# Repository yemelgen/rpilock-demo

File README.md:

This is my first project I have ever done with Rasperry PI.

It's simple and should be good as a learning example. 

I hope someone might find it useful.

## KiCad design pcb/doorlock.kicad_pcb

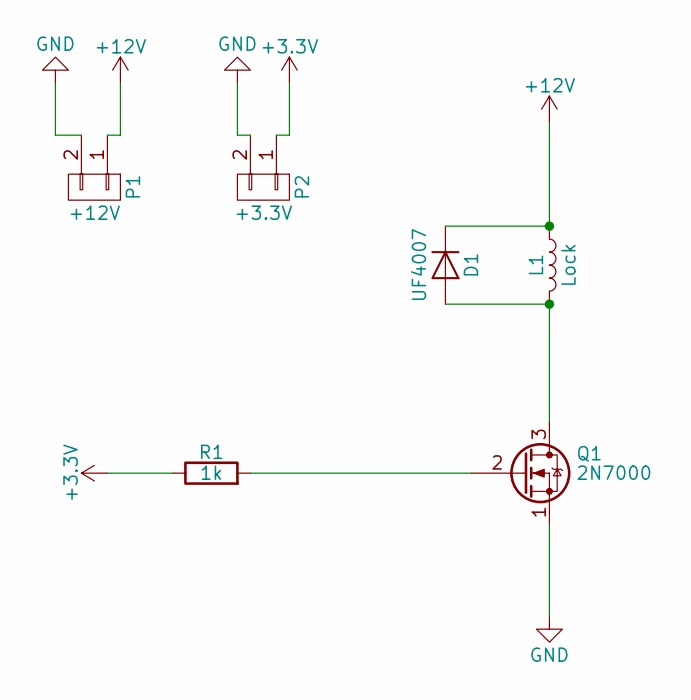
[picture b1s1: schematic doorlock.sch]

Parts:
D1: UF4007; D3
L1: Lock; Pin_Header_Straight_2x01
P1: +12V; Pin_Header_Straight_1x02
P2: +3.3V; Pin_Header_Straight_1x02
Q1: 2N7000; TO-92_Molded_Narrow
R1: 1k; R3

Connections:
+3V3: P2.1, R1.1
+12V: D1.1 (K), L1.1, P1.1
GND: P1.2, P2.2, Q1.1 (S)
unnamed: D1.2 (A), L1.2, Q1.3 (D)
unnamed: Q1.2 (G), R1.2

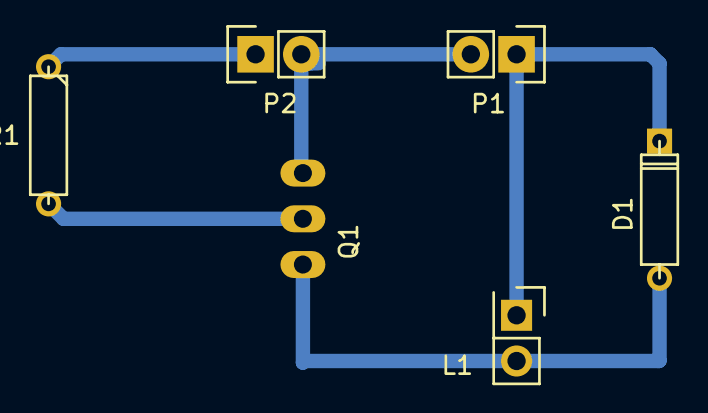
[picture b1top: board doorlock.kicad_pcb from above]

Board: 2 copper layers, 6 parts (0 on the bottom side), 5 nets.
